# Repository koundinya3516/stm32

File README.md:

# stm32
STM32F030C8T6-Based Custom PCB Design Designed a single-layer PCB in KiCad for the STM32F030C8T6 microcontroller, ensuring cost-effectiveness and compactness. Integrated GPIO expansion, power regulation, and peripheral interfacing while optimizing signal integrity and power management for efficient embedded applications.

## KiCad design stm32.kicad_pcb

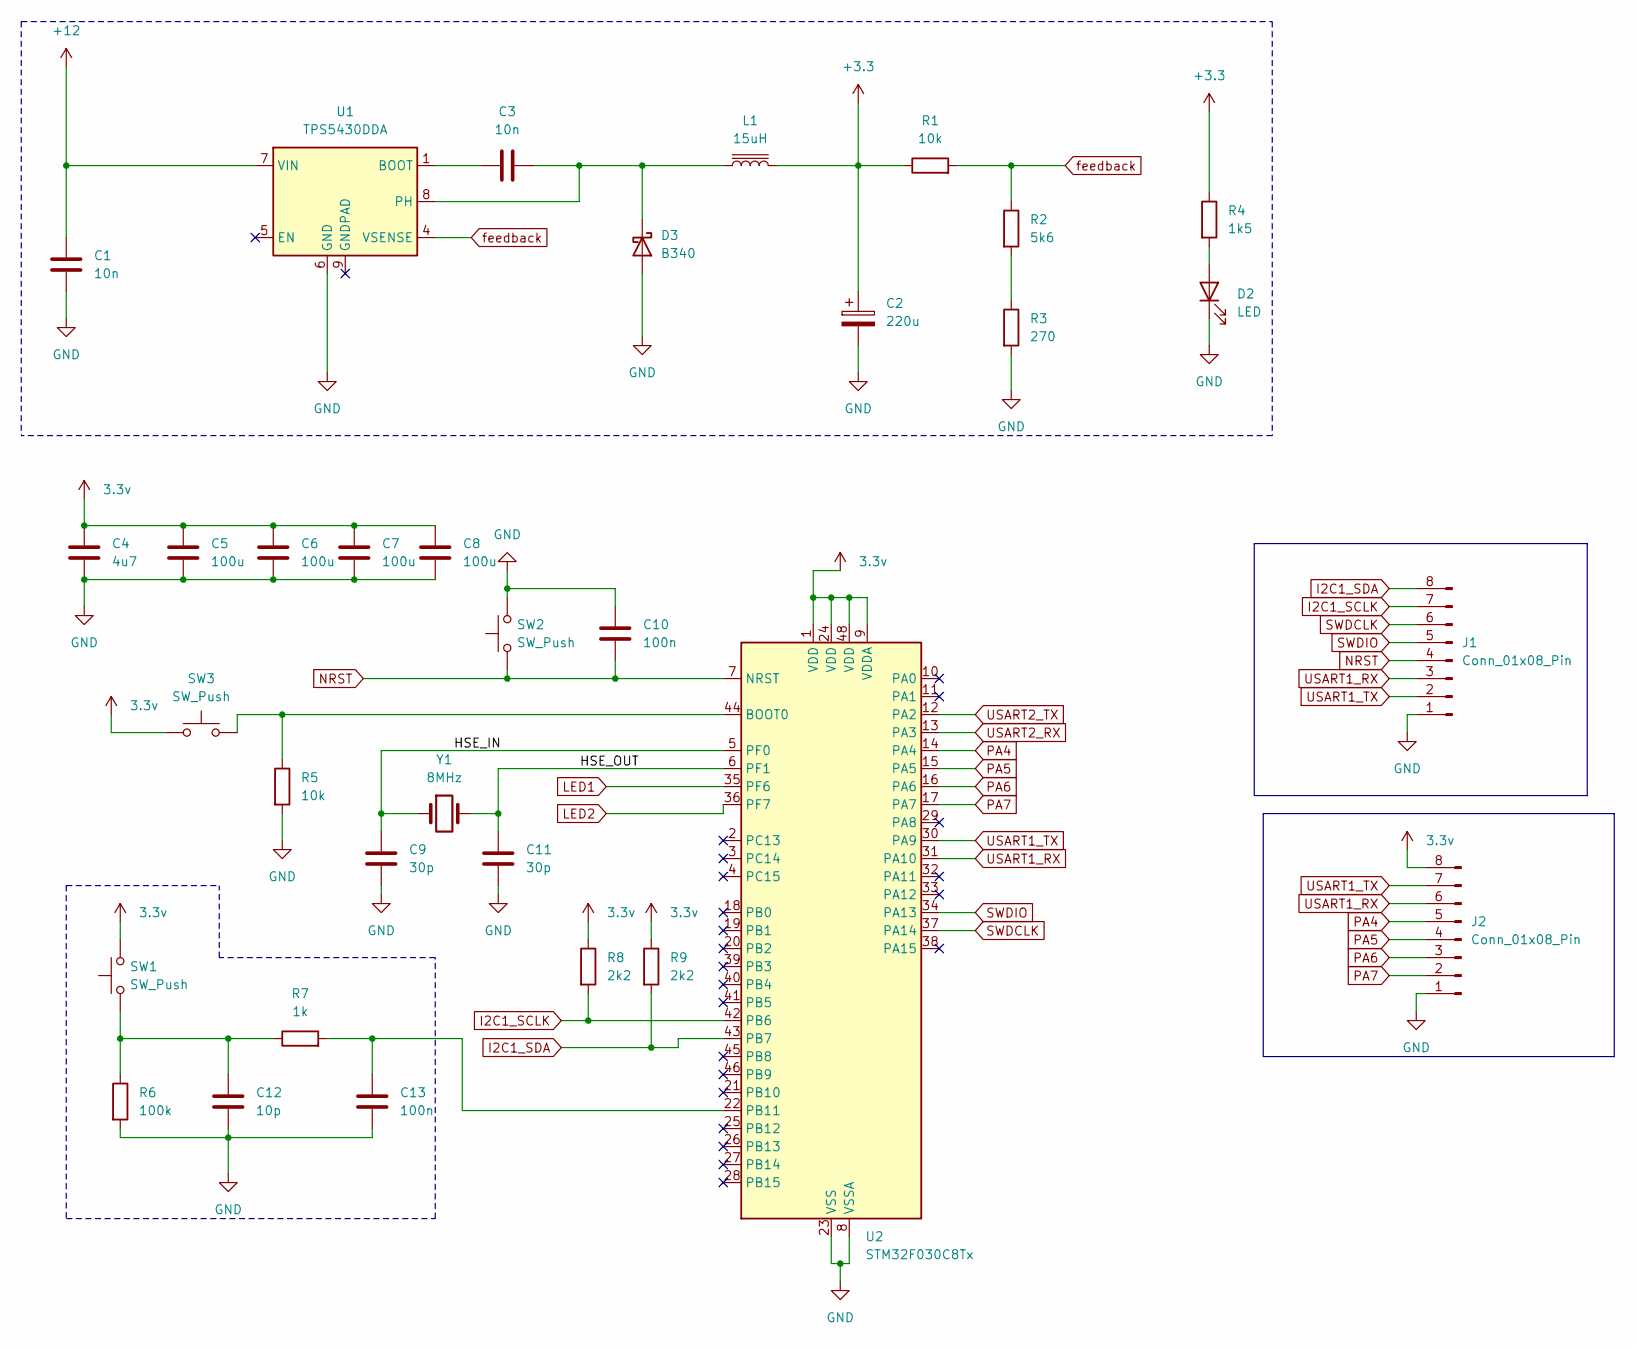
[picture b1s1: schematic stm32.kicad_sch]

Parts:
C1, C3: 10n; C_0201_0603Metric
C2: 220u; C_0201_0603Metric
C4: 4u7; C_0201_0603Metric
C5, C6, C7, C8: 100u; C_0201_0603Metric
C9, C11: 30p; C_0201_0603Metric
C10, C13: 100n; C_0201_0603Metric
C12: 10p; C_0201_0603Metric
D2: LED; LED_0402_1005Metric_Pad0.77x0.64mm_HandSolder
D3: B340; D_SMC
J1, J2: Conn_01x08_Pin; PinHeader_1x08_P2.54mm_Vertical
L1: 15uH; L_Changjiang_FNR8065S
R1, R5: 10k; R_0603_1608Metric_Pad0.98x0.95mm_HandSolder
R2: 5k6; R_0603_1608Metric_Pad0.98x0.95mm_HandSolder
R3: 270; R_0603_1608Metric_Pad0.98x0.95mm_HandSolder
R4: 1k5; R_0603_1608Metric_Pad0.98x0.95mm_HandSolder
R6: 100k; R_0603_1608Metric_Pad0.98x0.95mm_HandSolder
R7: 1k; R_0603_1608Metric_Pad0.98x0.95mm_HandSolder
R8, R9: 2k2; R_0603_1608Metric_Pad0.98x0.95mm_HandSolder
SW1, SW2, SW3: SW_Push; SW_SPST_PTS645
U1: TPS5430DDA; TI_SO-PowerPAD-8_ThermalVias
U2: STM32F030C8Tx; LQFP-48_7x7mm_P0.5mm
Y1: 8MHz; Crystal_HC18-U_Vertical

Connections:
3.3v: C4.2, C5.2, C6.2, C7.2, C8.2, J2.8, R8.1, R9.1, SW1.2, SW3.1, U2.1 (VDD), U2.9 (VDDA), U2.24 (VDD), U2.48 (VDD)
+3.3: C2.1, L1.2, R1.1, R4.1
+12: C1.1, U1.7 (VIN)
/HSE_IN: C9.1, U2.5 (PF0), Y1.1
/HSE_OUT: C11.1, U2.6 (PF1), Y1.2
GND: C1.2, C2.2, C4.1, C5.1, C6.1, C7.1, C8.1, C9.2, C10.1, C11.2, C12.2, C13.2, D2.1 (K), D3.2 (A), J1.1, J2.1, R3.2, R5.2, R6.2, SW2.2, U1.6 (GND), U2.8 (VSSA), U2.23 (VSS), U2.47 (VSS)
I2C1_SCLK: J1.7, R8.2, U2.42 (PB6)
I2C1_SDA: J1.8, R9.2, U2.43 (PB7)
LED1: U2.35 (PF6)
LED2: U2.36 (PF7)
NRST: C10.2, J1.4, SW2.1, U2.7 (NRST)
unnamed: C12.1, R6.1, R7.1, SW1.1
unnamed: D2.2 (A), R4.2
unnamed: C3.2, D3.1 (K), L1.1, U1.8 (PH)
unnamed: R2.2, R3.1
unnamed: C3.1, U1.1 (BOOT)
unnamed: R5.1, SW3.2, U2.44 (BOOT0)
unnamed: C13.1, R7.2, U2.22 (PB11)
PA4: J2.5, U2.14 (PA4)
PA5: J2.4, U2.15 (PA5)
PA6: J2.3, U2.16 (PA6)
PA7: J2.2, U2.17 (PA7)
SWDCLK: J1.6, U2.37 (PA14)
SWDIO: J1.5, U2.34 (PA13)
USART1_RX: J1.3, J2.6, U2.31 (PA10)
USART1_TX: J1.2, J2.7, U2.30 (PA9)
USART2_RX: U2.13 (PA3)
USART2_TX: U2.12 (PA2)
feedback: R1.2, R2.1, U1.4 (VSENSE)

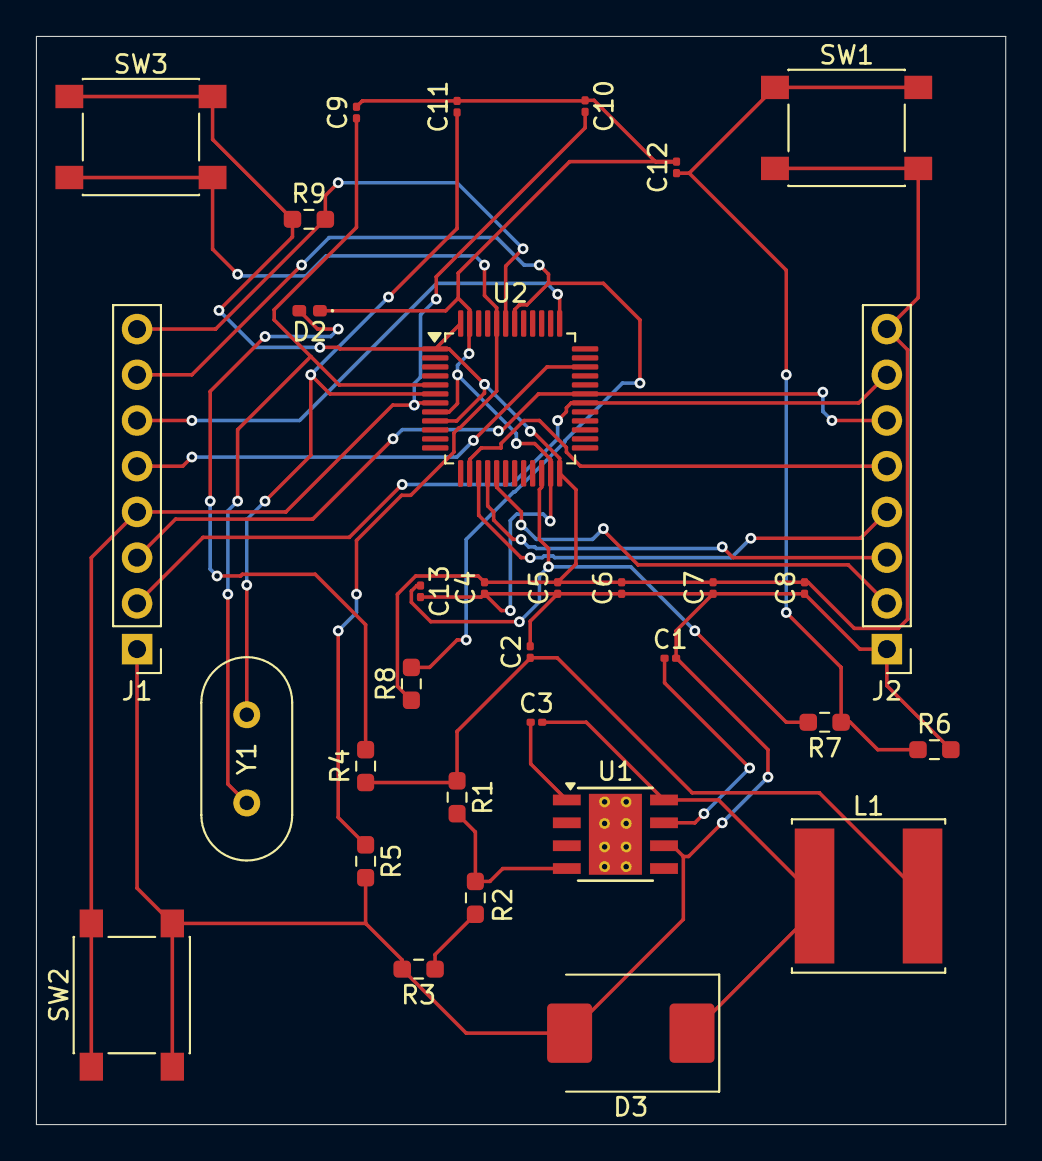
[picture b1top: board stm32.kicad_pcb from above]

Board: 2 copper layers, 53.8 x 60.5 mm, 33 parts (0 on the bottom side), 25 nets.
